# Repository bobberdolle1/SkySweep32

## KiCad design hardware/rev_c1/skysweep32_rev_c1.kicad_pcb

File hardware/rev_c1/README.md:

# SkySweep32 Rev C.1 Detector

**Status: `NO-GO — NOT ORDERABLE — NOT PRODUCTION VALIDATED`.**

This is an isolated Rev C.1 review tree based on `master` commit `51e48ccca8b64efdce41373d26b4c51c016152e0`. It does not modify Rev C. The only native-PCB change currently embodied here is the ESP32 antenna board-edge notch derived from the existing all-layer antenna keepout. The required power re-layout, USB reroute, 5.x detector, video-confirmation circuit, SkyPort circuit, updated enclosure and regenerated production outputs are **not yet represented in native KiCad sources**.

Therefore this directory is evidence for an engineering **NO-GO**, not a fabrication package. Do not send it to a board house or assembler.

Reviewed plans:

- `REV_C1_PREFAB_REVIEW.md` — independent finding disposition and every critical-IC gate.
- `DETECTOR_ARCHITECTURE.md` — selected 5.x filter-bin/log-detector and analog-video approach.
- `STACKUP_AND_IMPEDANCE.md` — current USB failure and required fabrication contract.
- `POWER_BUDGET.md` — revised allocation and power-path risks.
- `SKYPORT.md` — connector, protection, power and discovery contract.
- `PROCUREMENT_AND_COST.md` — supplier risk policy and budgetary China costs.
- `FIRST_ARTICLE_BRINGUP.md` — ordered bring-up/stop conditions.
- `DIPLOMA_VALIDATION_PLAN.md` — reproducible evidence experiments.

`validation/NATIVE_KICAD_CHECKS.md` records the native KiCad 10.0.5 result:
schematic ERC passes; the inherited/layout-incomplete PCB DRC fails. The failure
is a release blocker, not a waiver.

Native CAD can become fabrication authority only after all documented blockers are designed in, independently checked in KiCad 10, and manufacturing/mechanical outputs are regenerated from that checked source.

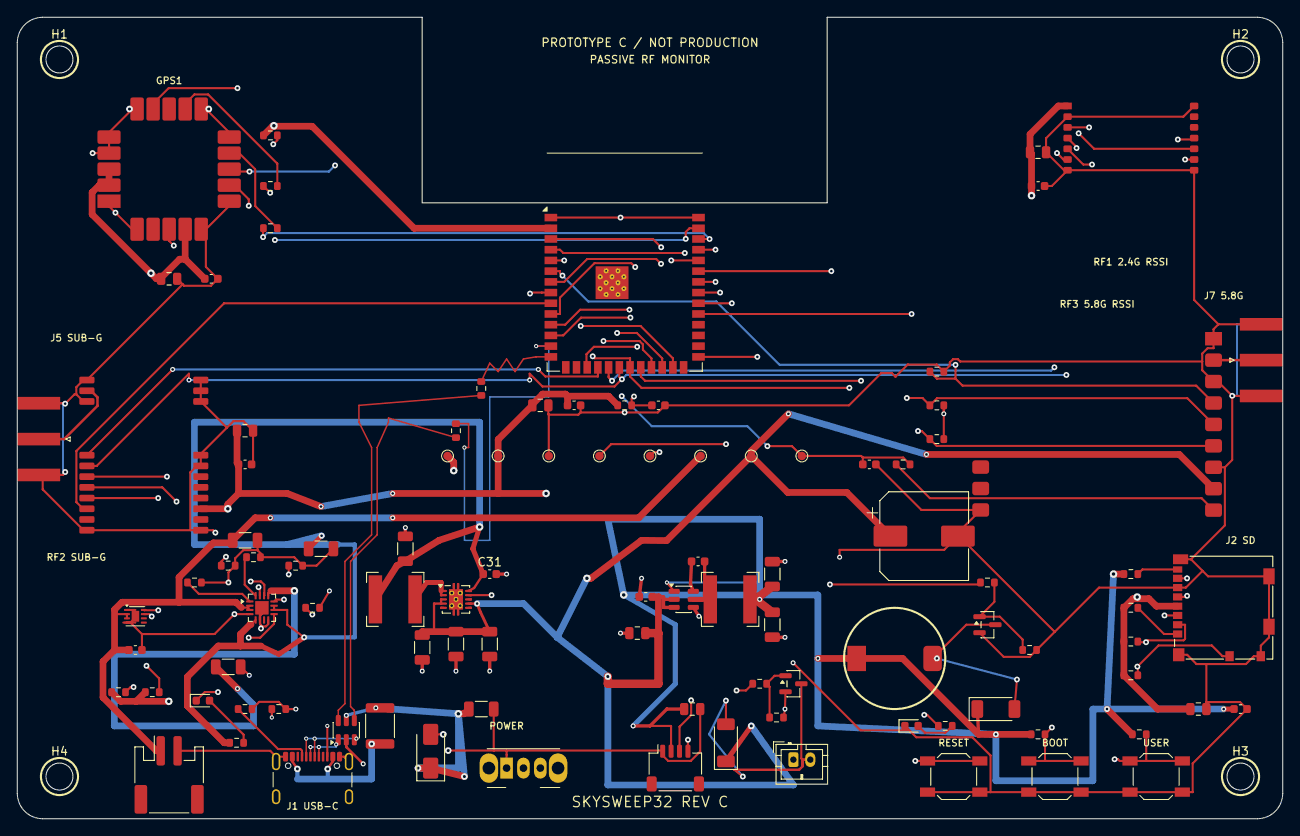
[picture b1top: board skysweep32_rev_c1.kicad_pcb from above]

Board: 4 copper layers, 150.0 x 95.0 mm, 104 parts (0 on the bottom side), 68 nets.

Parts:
BZ1: CMT-1203-SMT-TR; Buzzer_CUI_CMT_1203_SMT_TR
C1, C17, C18, C19: 10u; C_1206_3216Metric
C2, C6, C9, C11, C13, C15, C24, C29: 100n; C_0603_1608Metric
C3, C4, C20, C21, C22, C23: 22u; C_1206_3216Metric
C5, C8, C10, C12, C14, C16, C25: 10u; C_0805_2012Metric
C7: 1u; C_0603_1608Metric
C26: 470u 10V; CP_Elec_10x10
C30: 10n; C_0603_1608Metric
C31: 1uF 10V X7R; C_0603_1608Metric
D1: SMAJ5.0A; D_SMA
D2, D4: PMEG3020EP; D_SOD-128
D3: GREEN; LED_0603_1608Metric
D5: CHARGE; LED_0603_1608Metric
F1: MF-MSMF200-2; Fuse_1812_4532Metric
GPS1: SAM-M10Q-00B; Module_UBlox_SAM_M10Q
H1, H2, H3, H4: M3 NPTH / 10mm FASTENER KEEPOUT; MountingHole_M3_5mm_Keepout
J1: USB4105-GF-A; USB_C_Receptacle_GCT_USB4105-xx-A_16P_TopMnt_Horizontal
J2: Molex 104031-0811; microSD_HC_Molex_104031-0811
J3: OLED STEMMA QT; JST_SH_SM04B-SRSS-TB_1x04-1MP_P1.00mm_Horizontal
J4: OPTIONAL VIBRATION MOTOR; JST_PH_B2B-PH-K_1x02_P2.00mm_Vertical
J5: SUB-GHZ SMA; SMA_Amphenol_132289_EdgeMount
J6: BATTERY — ADAFRUIT PID 328; JST_PH_S2B-PH-SM4-TB_1x02-1MP_P2.00mm_Horizontal
J7: 5.8-GHZ SMA; SMA_Amphenol_132289_EdgeMount
L1: 3.9uH SRN6028-3R9M; L_Bourns-SRN6028
L2: 1uH SRN6028C-1R0Y; L_Bourns-SRN6028
Q1, Q2: AO3400A; SOT-23
R1, R2: 5.1k; R_0603_1608Metric
R3, R4: 22R; R_0603_1608Metric
R5, R6, R7, R8, R20: 10k; R_0603_1608Metric
R9, R10: 0R; R_0603_1608Metric
R11, R12, R13, R14: 47k; R_0603_1608Metric
R15, R18: 100R; R_0603_1608Metric
R16, R19, R28, R29, R30: 100k; R_0603_1608Metric
R17, R31: 1k; R_0603_1608Metric
R21: 46.4k; R_0603_1608Metric
R22: 1.13k; R_0603_1608Metric
R23: 1.18k; R_0603_1608Metric
R24: 4.12k; R_0603_1608Metric
R25: 1.5k; R_0603_1608Metric
R26, R27: 4.7k; R_0603_1608Metric
RF1: E28-2G4M12SX; Module_Ebyte_E28_2G4M12SX
RF2: E07-900M10S; Module_Ebyte_E07_900M10S
RF3: RX5808-2012-12P; Module_RX5808_2012_12P
SW1: RESET; SW_SPST_SKQG_WithoutStem
SW2: BOOT; SW_SPST_SKQG_WithoutStem
SW3: USER; SW_SPST_SKQG_WithoutStem
SW4: SYSTEM POWER; SW_Slide_SPDT_Angled_CK_OS102011MA1Q
TP1: VBUS_PROTECTED; TestPoint_Pad_D1.0mm
TP2: 3V3; TestPoint_Pad_D1.0mm
TP3: GND; TestPoint_Pad_D1.0mm
TP4: UART0_TX; TestPoint_Pad_D1.0mm
TP5: UART0_RX; TestPoint_Pad_D1.0mm
TP6: BAT_CELL; TestPoint_Pad_D1.0mm
TP7: SYS_5V; TestPoint_Pad_D1.0mm
TP8: RX5808_RSSI_ADC; TestPoint_Pad_D1.0mm
U1: ESP32-S3-WROOM-1-N16R8; ESP32-S3-WROOM-1_AntennaNotch
U2: USBLC6-2SC6; SOT-23-6
U3: AP63203WU-7; TSOT-23-6
U4: BQ24074RGTR; VQFN-16-1EP_3x3mm_P0.5mm_EP1.6x1.6mm
U5: TPS61232DRCR; Texas_S-PVSON-N10_ThermalVias
U6: MAX17048G+T10; DFN-8-1EP_2x2mm_P0.5mm_EP0.9x1.3mm

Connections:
3V3: BZ1.1, C3.1, C4.1, C5.1, C6.1, C8.1, C9.1, C10.1, C11.1, C12.1, C13.1, C14.1, C15.1, C16.1, D2.1, GPS1.2, GPS1.3, GPS1.17, J2.4, J3.2, L1.2, R5.1, R6.1, R7.1, R8.1, R11.1, R12.1, R13.1, R14.1, R26.1, R27.1, RF1.1, RF2.9, TP2.1, U1.2, U3.1
ALERT_BUZZER_GATE: R15.1, U1.32
ALERT_BUZZER_GATE_R: Q1.1, R15.2, R16.1
ALERT_LED: R17.1, U1.33
BAT_CELL: C18.1, C29.1, J6.1, TP6.1, U4.2, U4.3, U6.2, U6.3
BOOST_EN: SW4.2, U5.9
BOOST_SW: L2.2, U5.1, U5.2
BOOT_N: R6.2, SW2.1, U1.27
BQ_ILIM: R23.1, U4.12
BQ_ISET: R22.1, U4.16
BQ_ITERM: R24.1, U4.15
BQ_TMR: R21.1, U4.14
BQ_TS: R20.1, U4.1
BUCK_BST: C2.1, U3.6
BUCK_SW: C2.2, L1.1, U3.5
BUZZER_DRAIN: BZ1.2, D2.2, Q1.3
CC1101_CSN: RF2.19, U1.18
CC1101_GDO0: RF2.15, U1.8
CC1101_GDO2: RF2.14, U1.9
CHG_LED_A: D5.2, R25.2
CHG_N: D5.1, U4.9
GND: C1.2, C3.2, C4.2, C5.2, C6.2, C7.2, C8.2, C9.2, C10.2, C11.2, C12.2, C13.2, C14.2, C15.2, C16.2, C17.2, C18.2, C19.2, C20.2, C21.2, C22.2, C23.2, C24.2, C25.2, C26.2, C29.2, C30.2, C31.2, D1.2, D3.1, GPS1.1, GPS1.4, GPS1.5, GPS1.6, GPS1.10, GPS1.11, GPS1.15, GPS1.16, GPS1.20, J1.A1, J1.A12, J1.B1, J1.B12, J1.SH, J2.6, J2.10, J2.SH, J3.1, J5.2, J6.2, J7.2, Q1.2, Q2.2, R1.2, R2.2, R16.2, R19.2, R20.2, R21.2, R22.2, R23.2, R24.2, R28.2, R29.2, R30.2, RF1.2, RF1.7, RF1.8, RF1.14, RF2.1, RF2.2, RF2.3, RF2.4, RF2.5, RF2.11, RF2.12, RF2.20, RF2.22, RF3.1, RF3.3, RF3.7, RF3.12, SW1.2, SW2.2, SW3.2, SW4.1, TP3.1, U1.1, U1.40, U1.41, U2.2, U3.4, U4.4, U4.6, U4.8, U4.17, U5.11, U6.1, U6.4, U6.9
GPS_I2C_SCL: GPS1.12, R10.2
GPS_I2C_SDA: GPS1.9, R9.2
GPS_PPS: GPS1.7, U1.23
GPS_RESET_N: GPS1.18, R8.2
GPS_RX: GPS1.13, U1.24
GPS_TX: GPS1.14, U1.25
I2C_SCL: J3.4, R10.1, R27.2, U1.38, U6.7
I2C_SDA: J3.3, R9.1, R26.2, U1.39, U6.8
MCU_EN: C7.1, R5.2, SW1.1, U1.3
RF_SPI_MISO: J2.7, RF1.3, RF2.16, U1.21
RF_SPI_MOSI: J2.3, RF1.4, RF2.17, U1.19
RF_SPI_SCK: J2.5, RF1.5, RF2.18, U1.20
RX5808_CH1: R28.1, RF3.4, U1.6
RX5808_CH2: R29.1, RF3.5, U1.7
RX5808_CH3: R30.1, RF3.6, U1.22
RX5808_RF_IN: J7.1, RF3.2
RX5808_RSSI_ADC: C30.1, R31.2, TP8.1, U1.5
RX5808_RSSI_RAW: R31.1, RF3.9
SD_CSN: J2.2, R13.2, U1.31
SD_DAT1: J2.8, R11.2
SD_DAT2: J2.1, R12.2
SD_DETECT: J2.9, R14.2, U1.4
STATUS_LED_A: D3.2, R17.2
SUBGHZ_ANT: J5.1, RF2.21
SX1281_BUSY: RF1.10, U1.12
SX1281_CSN: RF1.6, U1.17
SX1281_DIO1: RF1.11, U1.11
SX1281_RESET: RF1.9, U1.10
SYS_5V: C21.1, C22.1, C23.1, C24.1, C25.1, C26.1, D4.1, J4.1, RF3.8, TP7.1, U3.2, U3.3, U5.3, U5.4, U5.7
UART0_RX: TP5.1, U1.36
UART0_TX: TP4.1, U1.37
USB_CC1: J1.A5, R1.1
USB_CC2: J1.B5, R2.1
USB_D_N: R4.2, U1.13
USB_D_N_CONN: J1.A7, J1.B7, U2.3
USB_D_N_ESD: R4.1, U2.4
USB_D_P: R3.2, U1.14
USB_D_P_CONN: J1.A6, J1.B6, U2.1
USB_D_P_ESD: R3.1, U2.6
USER_BUTTON_N: R7.2, SW3.1, U1.35
VBUS_PROTECTED: C1.1, C17.1, D1.1, F1.2, TP1.1, U2.5, U4.13
VBUS_RAW: F1.1, J1.A4, J1.A9, J1.B4, J1.B9
VIBRATION_DRAIN: D4.2, J4.2, Q2.3
VIBRATION_GATE: R18.1, U1.34
VIBRATION_GATE_R: Q2.1, R18.2, R19.1
VSYS_BAT: C19.1, C20.1, C31.1, L2.1, R25.1, SW4.3, U4.5, U4.10, U4.11, U5.10

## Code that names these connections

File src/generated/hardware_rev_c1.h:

// Generated by tools/development/generate_rev_c1_pinmap.py; do not edit.
// Source: hardware/rev_c1/hardware_manifest.json
#pragma once

#define BOARD_SKYSWEEP32_REV_C1 1
#define PROFILE_PASSIVE_DETECTOR 1

#define MODULE_SX1281 1
#define MODULE_CC1101 1
#define MODULE_RX5808 1
#define MODULE_FIVE_X_DETECTOR 1
#define MODULE_ANALOG_VIDEO 1
#define MODULE_SKYPORT 1
#define MODULE_BATTERY_GAUGE 1
#define MODULE_OLED 1
#define MODULE_WEB_SERVER 1
#define MODULE_GPS 1
#define MODULE_SD_CARD 1
#define MODULE_ESPNOW 1

#define PIN_I2C_SDA              1  // I2C_SDA
#define PIN_I2C_SCL              2  // I2C_SCL
#define PIN_SD_DETECT            4  // SD_DETECT
#define PIN_RX5808_RSSI          5  // RX5808_RSSI
#define PIN_RX5808_CH1           6  // RX5808_CH1
#define PIN_RX5808_CH2           7  // RX5808_CH2
#define PIN_SX1281_BUSY          8  // SX1281_BUSY
#define PIN_SX1281_CS            9  // SX1281_CSN
#define PIN_CC1101_CS            10 // CC1101_CSN
#define PIN_SPI_MOSI             11 // RF_SPI_MOSI
#define PIN_SPI_SCK              12 // RF_SPI_SCK
#define PIN_SPI_MISO             13 // RF_SPI_MISO
#define PIN_RX5808_CH3           14 // RX5808_CH3
#define PIN_CC1101_GDO0          15 // CC1101_GDO0
#define PIN_CC1101_GDO2          16 // CC1101_GDO2
#define PIN_SX1281_RESET         17 // SX1281_RESET
#define PIN_SX1281_DIO1          18 // SX1281_DIO1
#define PIN_GPS_PPS              21 // GPS_PPS
#define PIN_SD_CS                38 // SD_CSN
#define PIN_BUZZER               39 // ALERT_BUZZER
#define PIN_ALERT_LED            40 // ALERT_LED
#define PIN_VIBRATION            41 // VIBRATION
#define PIN_USER_BUTTON          42 // USER_BUTTON
#define PIN_GPS_RX               47 // GPS_RX
#define PIN_GPS_TX               48 // GPS_TX
#define PIN_FIVE_X_FILTER_LOW    22 // FIVE_X_FILTER_LOW
#define PIN_FIVE_X_FILTER_HIGH   23 // FIVE_X_FILTER_HIGH
#define PIN_VIDEO_SYNC           24 // VIDEO_SYNC
#define PIN_SKYPORT_5V_EN        25 // SKYPORT_5V_EN
#define PIN_SKYPORT_3V3_EN       26 // SKYPORT_3V3_EN
#define PIN_SKYPORT_DETECT       27 // SKYPORT_DETECT
#define PIN_SKYPORT_IRQ          28 // SKYPORT_IRQ
#define PIN_SKYPORT_UART_RX      29 // SKYPORT_UART_RX
#define PIN_SKYPORT_UART_TX      30 // SKYPORT_UART_TX
#define PIN_SKYPORT_SPI_CS       31 // SKYPORT_SPI_CS
#define PIN_SKYPORT_RESET        32 // SKYPORT_RESET
#define PIN_SD_MOSI             PIN_SPI_MOSI // shared SPI data
#define PIN_SD_MISO             PIN_SPI_MISO // shared SPI data
#define PIN_SD_SCK              PIN_SPI_SCK  // shared SPI clock

#define GPS_BAUD_RATE            9600
#define GPS_UPDATE_INTERVAL      1000

#if defined(TIER_JUGGERNAUT) || defined(ENABLE_COUNTERMEASURES)
#error "Rev C.1 is passive-only and has no countermeasure hardware"
#endif
#if defined(MODULE_NRF24) || defined(MODULE_LORA) || defined(MODULE_ML)
#error "Rev C.1 does not implement nRF24L01+, LoRa, or TinyML hardware/features"
#endif
#ifdef MODULE_ACOUSTIC
#error "Rev C.1 does not route an I2S acoustic input"
#endif

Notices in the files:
hardware/rev_c1/skysweep32_rev_c1.kicad_pcb:
GPL-3.0-only | github.com/bobberdolle1/SkySweep32
